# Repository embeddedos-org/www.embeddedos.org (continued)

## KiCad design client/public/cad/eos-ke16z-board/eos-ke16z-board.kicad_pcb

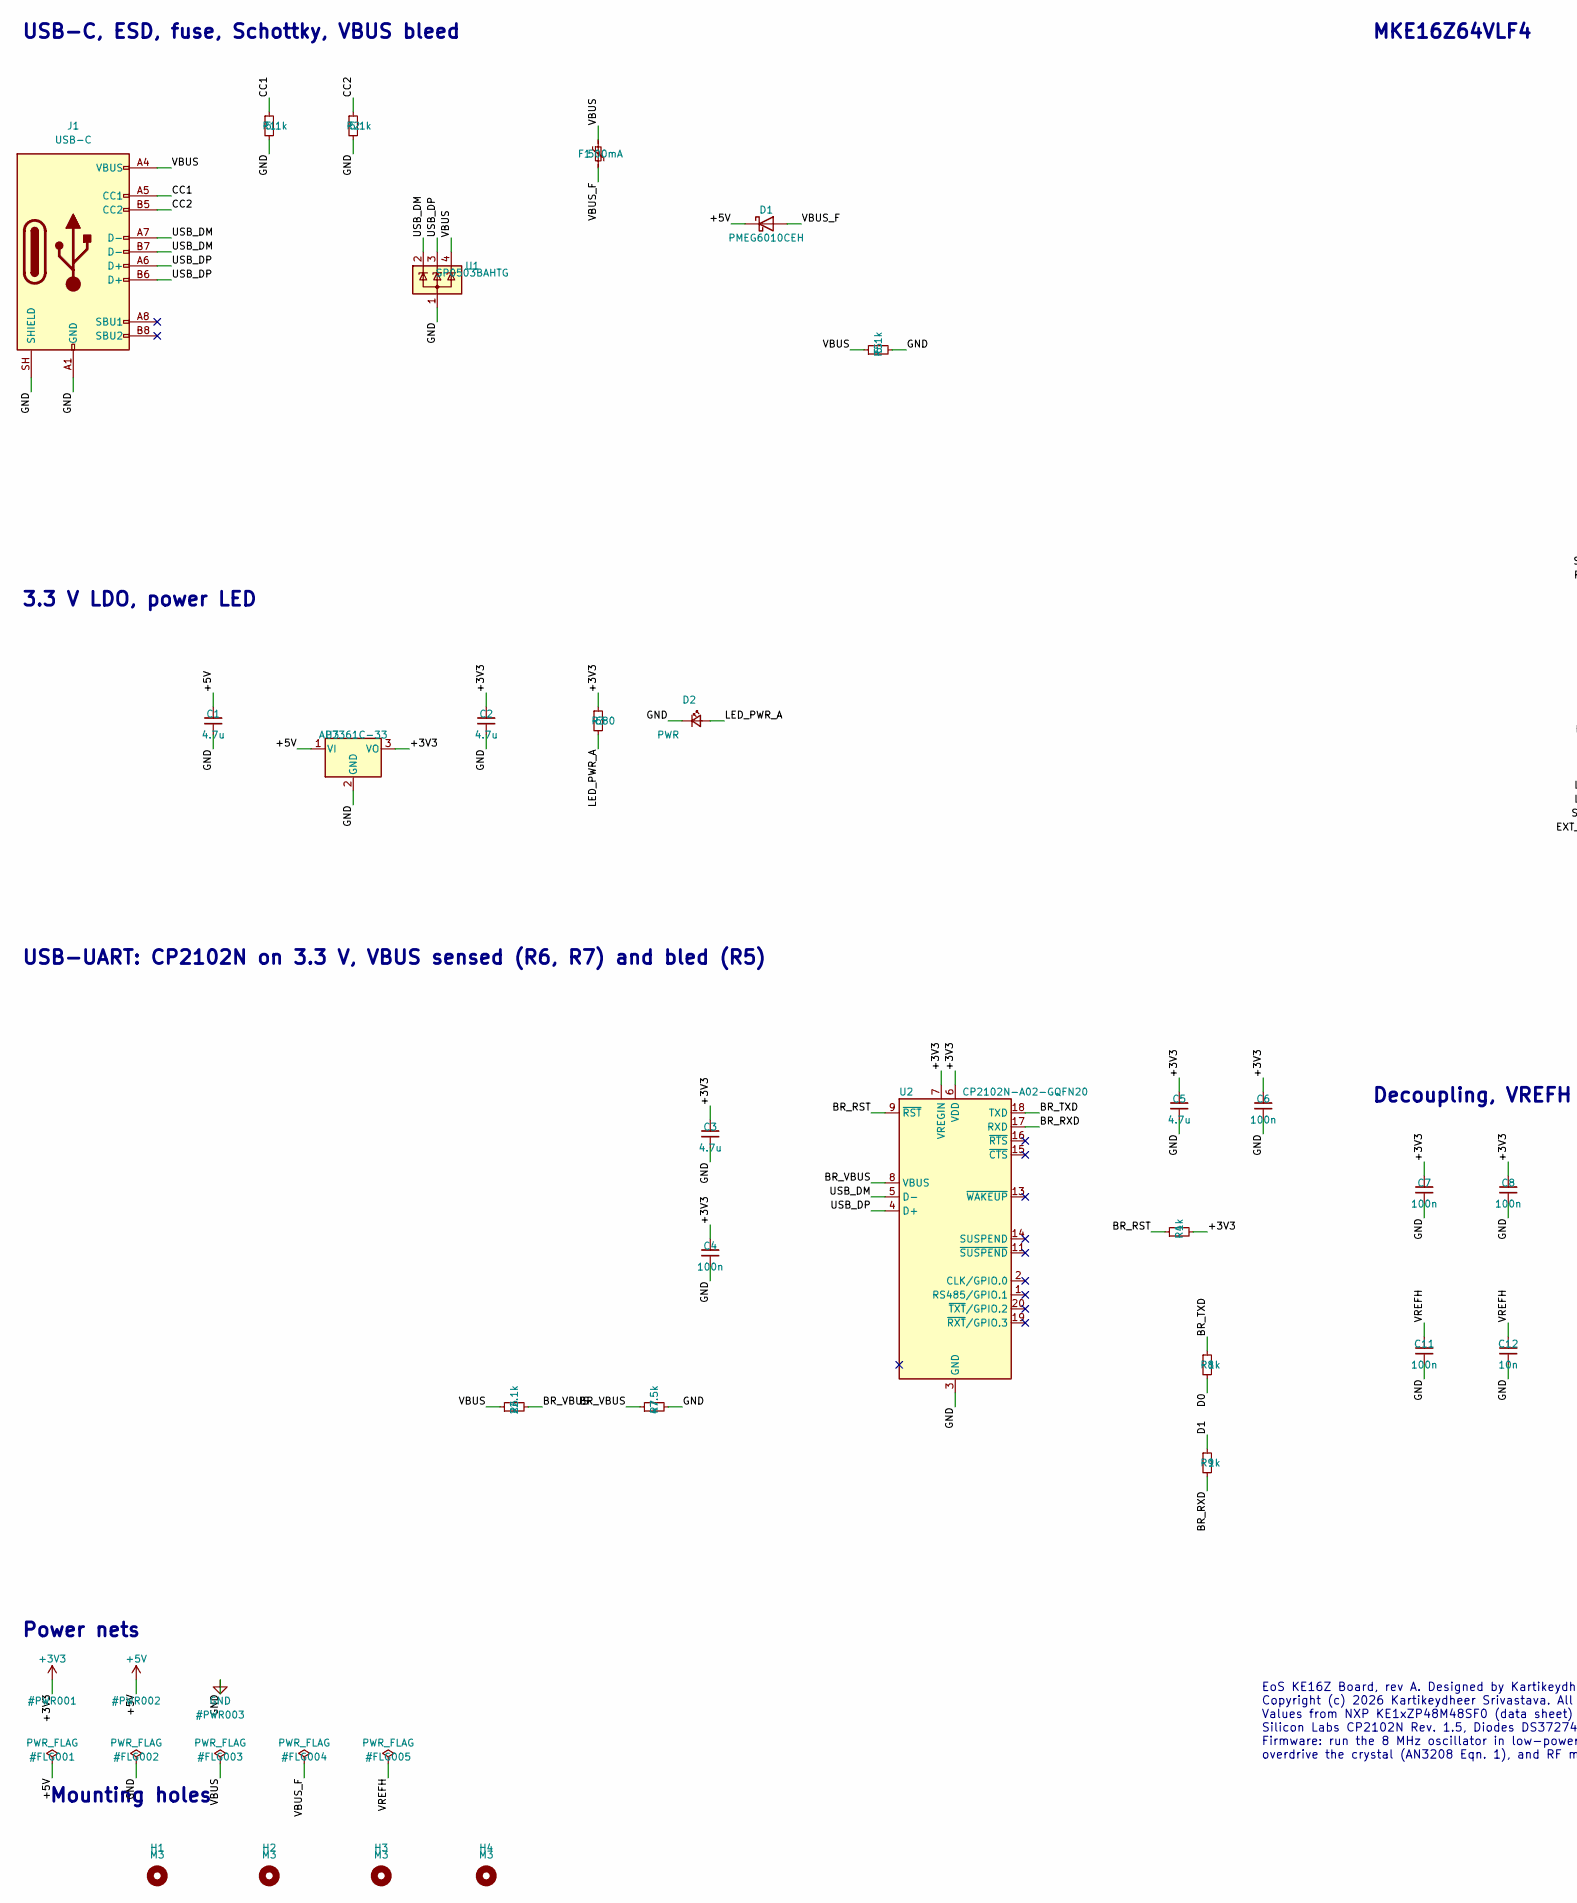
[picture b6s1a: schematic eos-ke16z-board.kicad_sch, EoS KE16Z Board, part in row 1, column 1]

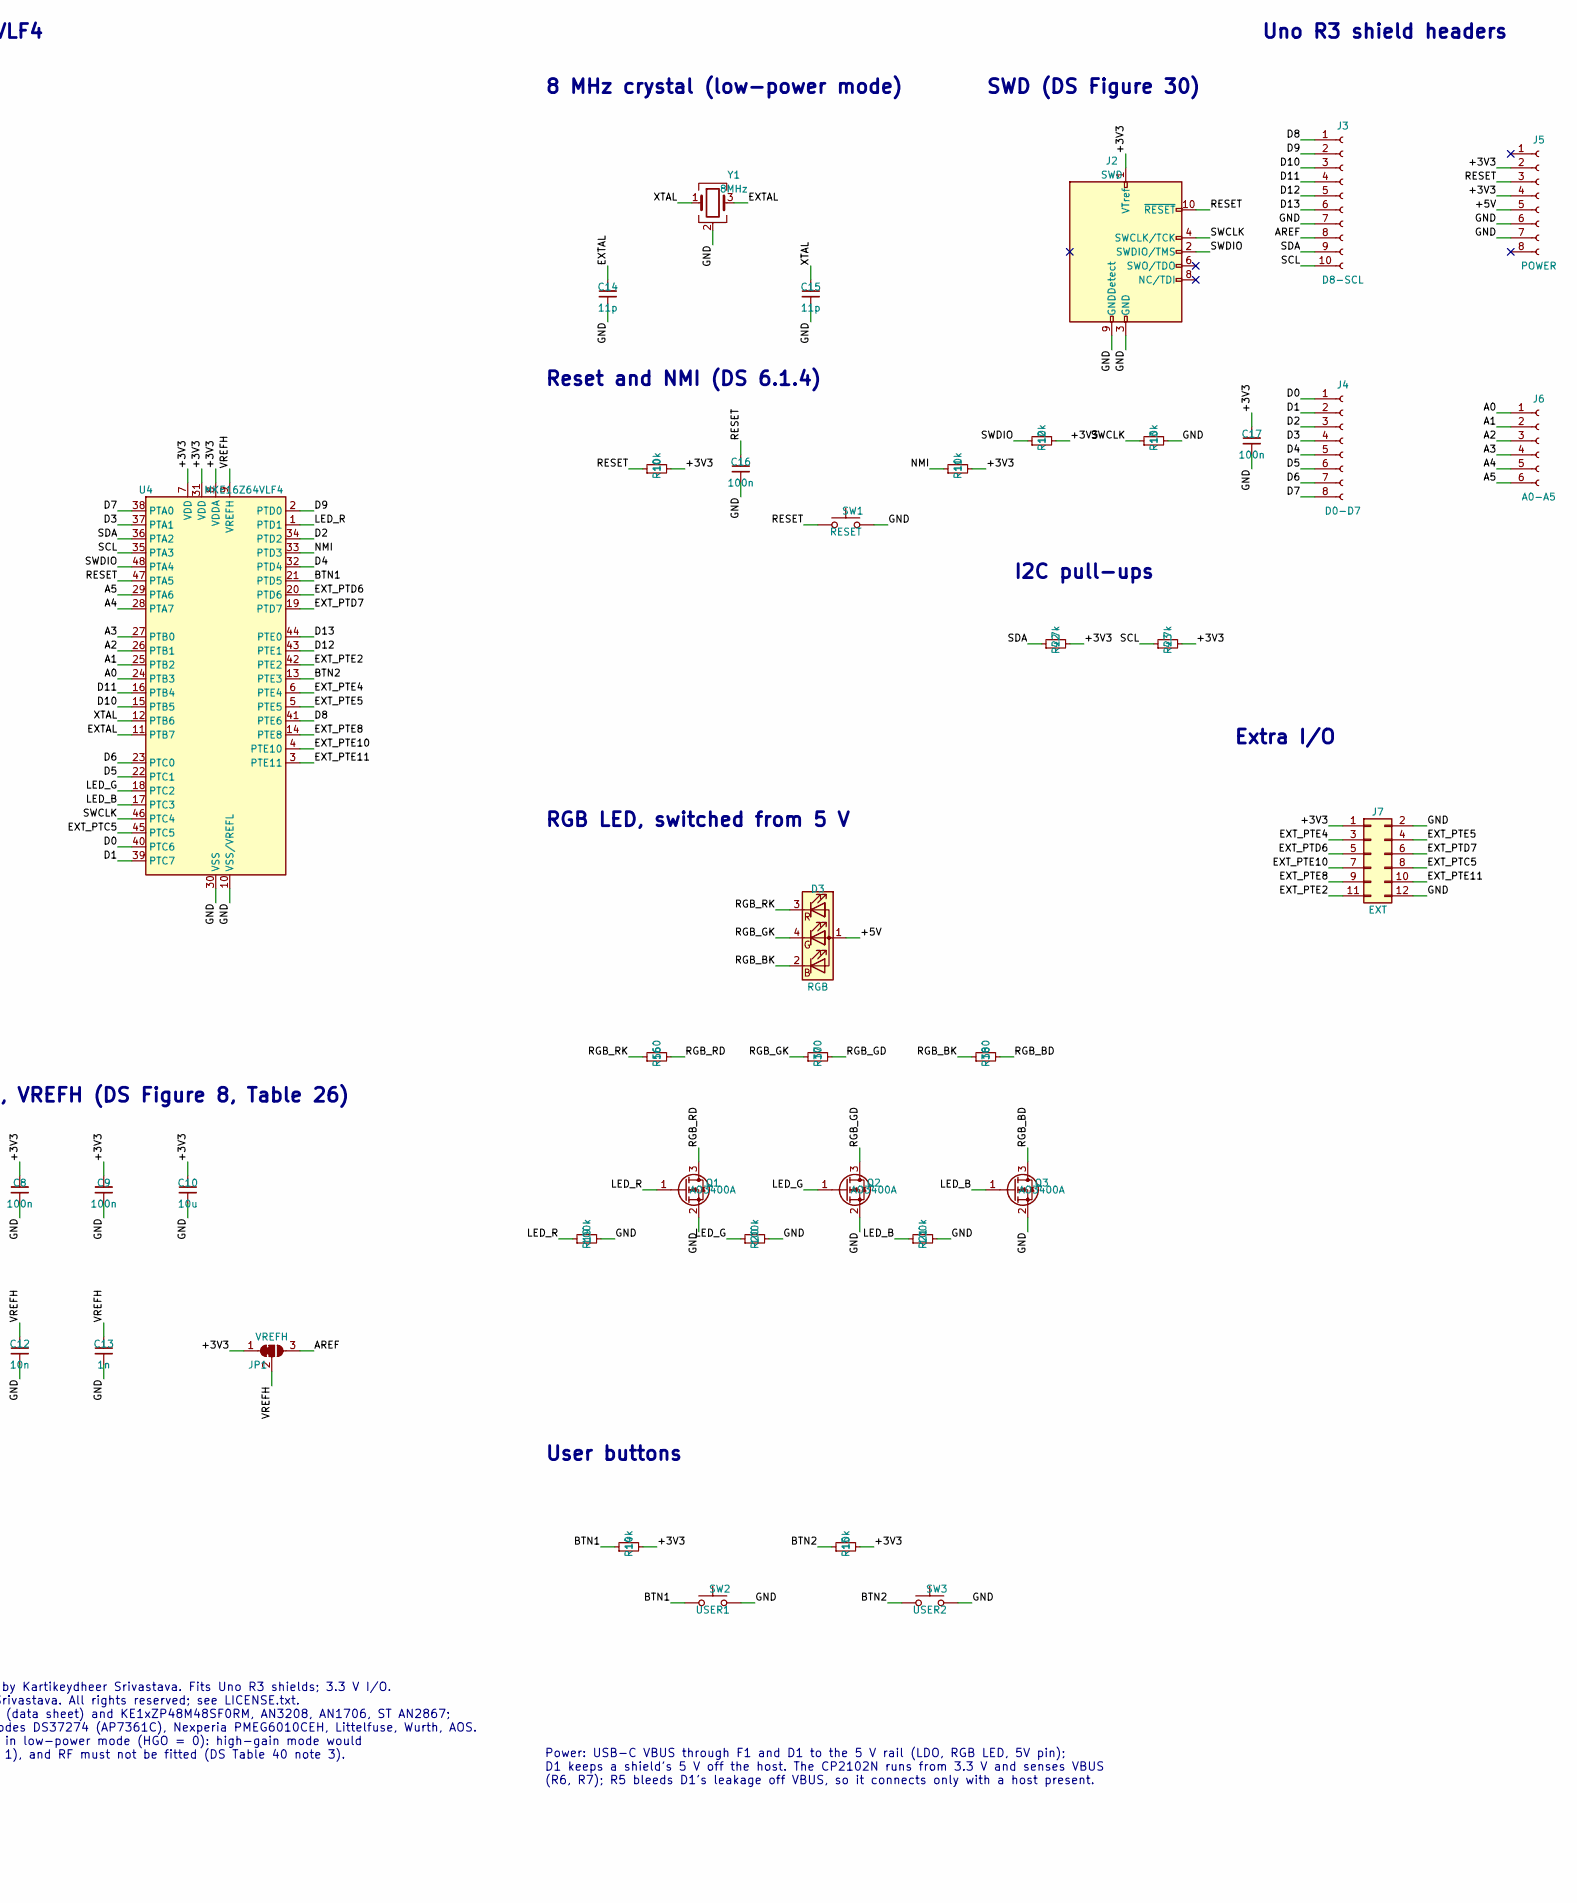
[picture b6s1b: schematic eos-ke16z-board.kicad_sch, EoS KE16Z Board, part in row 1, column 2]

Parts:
C1: 4.7u; C_0805_2012Metric; MPN GRM219R61E475KA73D
C2, C3, C5: 4.7u; C_0805_2012Metric; MPN GRM21BR71A475KE51L
C4, C6, C7, C8, C9, C11, C16, C17: 100n; C_0402_1005Metric; MPN GRM155R71C104KA88D
C10: 10u; C_0805_2012Metric; MPN GRM21BR61C106KE15L
C12: 10n; C_0402_1005Metric; MPN GRM155R71H103KA88D
C13: 1n; C_0402_1005Metric; MPN GRM1555C1H102JA01D
C14, C15: 11p; C_0402_1005Metric; MPN GJM1555C1H110JB01D
D1: PMEG6010CEH; D_SOD-123F; MPN PMEG6010CEH
D2: PWR; LED_0603_1608Metric; MPN APTD1608LCGCK
D3: RGB; LED_RGB_Wuerth-PLCC4_3.2x2.8mm_150141M173100; MPN 150141M173100
F1: 500mA; Fuse_1206_3216Metric; MPN 1206L050YR
H1, H2, H3, H4: M3; MountingHole_3.2mm_M3_ISO14580
J1: USB-C; USB_C_Receptacle_HRO_TYPE-C-31-M-12; MPN TYPE-C-31-M-12
J2: SWD; PinHeader_2x05_P1.27mm_Vertical_SMD; MPN FTSH-105-01-L-DV-K
J3: D8-SCL; PinSocket_1x10_P2.54mm_Vertical; MPN SSW-110-01-T-S
J4: D0-D7; PinSocket_1x08_P2.54mm_Vertical; MPN SSW-108-01-T-S
J5: POWER; PinSocket_1x08_P2.54mm_Vertical; MPN SSW-108-01-T-S
J6: A0-A5; PinSocket_1x06_P2.54mm_Vertical; MPN SSW-106-01-T-S
J7: EXT; PinHeader_2x06_P2.54mm_Vertical; MPN TSW-106-07-G-D
JP1: VREFH; SolderJumper-3_P1.3mm_Bridged12_RoundedPad1.0x1.5mm
Q1, Q2, Q3: AO3400A; SOT-23; MPN AO3400A
R1, R2, R5: 5.1k; R_0402_1005Metric; MPN RC0402FR-075K1L
R3: 680; R_0402_1005Metric; MPN RC0402FR-07680RL
R4, R8, R9: 1k; R_0402_1005Metric; MPN RC0402FR-071KL
R6: 22.1k; R_0402_1005Metric; MPN RC0402FR-0722K1L
R7: 47.5k; R_0402_1005Metric; MPN RC0402FR-0747K5L
R10, R11, R12, R13, R14, R15: 10k; R_0402_1005Metric; MPN RC0402FR-0710KL
R16: 560; R_0402_1005Metric; MPN RC0402FR-07560RL
R17, R18: 300; R_0402_1005Metric; MPN RC0402FR-07300RL
R19, R20, R21: 100k; R_0402_1005Metric; MPN RC0402FR-07100KL
R22, R23: 4.7k; R_0402_1005Metric; MPN RC0402FR-074K7L
SW1: RESET; SW_Push_1P1T_NO_CK_KMR2; MPN KMR221G LFS
SW2: USER1; SW_Push_1P1T_NO_CK_KMR2; MPN KMR221G LFS
SW3: USER2; SW_Push_1P1T_NO_CK_KMR2; MPN KMR221G LFS
U1: SP0503BAHTG; SOT-143; MPN SP0503BAHTG
U2: CP2102N-A02-GQFN20; SiliconLabs_QFN-20-1EP_3x3mm_P0.5mm_EP1.8x1.8mm; MPN CP2102N-A02-GQFN20
U3: AP7361C-33; SOT-223-3_TabPin2; MPN AP7361C-33E-13
U4: MKE16Z64VLF4; LQFP-48_7x7mm_P0.5mm; MPN MKE16Z64VLF4
Y1: 8MHz; Crystal_SMD_5032-4Pin_5.0x3.2mm; MPN ECS-80-10-30B-CWN-TR

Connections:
+3V3: C2.1, C3.1, C4.1, C5.1, C6.1, C7.1, C8.1, C9.1, C10.1, C17.1, J2.1 (VTref), J5.2, J5.4, J7.1, JP1.1 (A), R3.1, R4.2, R10.2, R11.2, R12.2, R14.2, R15.2, R22.2, R23.2, U2.6 (VDD), U2.7 (VREGIN), U3.3 (VO), U4.7 (VDD), U4.8 (VDDA), U4.31 (VDD)
+5V: C1.1, D1.1 (K), D3.1 (A), J5.5, U3.1 (VI)
/A0: J6.1, U4.24 (PTB3)
/A1: J6.2, U4.25 (PTB2)
/A2: J6.3, U4.26 (PTB1)
/A3: J6.4, U4.27 (PTB0)
/A4: J6.5, U4.28 (PTA7)
/A5: J6.6, U4.29 (PTA6)
/AREF: J3.8, JP1.3 (B)
/BR_RST: R4.1, U2.9 (~RST)
/BR_RXD: R9.2, U2.17 (RXD)
/BR_TXD: R8.1, U2.18 (TXD)
/BR_VBUS: R6.2, R7.1, U2.8 (VBUS)
/BTN1: R14.1, SW2.1, U4.21 (PTD5)
/BTN2: R15.1, SW3.1, U4.13 (PTE3)
/CC1: J1.A5 (CC1), R1.1
/CC2: J1.B5 (CC2), R2.1
/D0: J4.1, R8.2, U4.40 (PTC6)
/D1: J4.2, R9.1, U4.39 (PTC7)
/D2: J4.3, U4.34 (PTD2)
/D3: J4.4, U4.37 (PTA1)
/D4: J4.5, U4.32 (PTD4)
/D5: J4.6, U4.22 (PTC1)
/D6: J4.7, U4.23 (PTC0)
/D7: J4.8, U4.38 (PTA0)
/D8: J3.1, U4.41 (PTE6)
/D9: J3.2, U4.2 (PTD0)
/D10: J3.3, U4.15 (PTB5)
/D11: J3.4, U4.16 (PTB4)
/D12: J3.5, U4.43 (PTE1)
/D13: J3.6, U4.44 (PTE0)
/EXTAL: C14.1, U4.11 (PTB7), Y1.3
/EXT_PTC5: J7.8, U4.45 (PTC5)
/EXT_PTD6: J7.5, U4.20 (PTD6)
/EXT_PTD7: J7.6, U4.19 (PTD7)
/EXT_PTE2: J7.11, U4.42 (PTE2)
/EXT_PTE4: J7.3, U4.6 (PTE4)
/EXT_PTE5: J7.4, U4.5 (PTE5)
/EXT_PTE8: J7.9, U4.14 (PTE8)
/EXT_PTE10: J7.7, U4.4 (PTE10)
/EXT_PTE11: J7.10, U4.3 (PTE11)
/LED_B: Q3.1 (G), R21.1, U4.17 (PTC3)
/LED_G: Q2.1 (G), R20.1, U4.18 (PTC2)
/LED_PWR_A: D2.2 (A), R3.2
/LED_R: Q1.1 (G), R19.1, U4.1 (PTD1)
/NMI: R11.1, U4.33 (PTD3)
/RESET: C16.1, J2.10 (~RESET), J5.3, R10.1, SW1.1, U4.47 (PTA5)
/RGB_BD: Q3.3 (D), R18.2
/RGB_BK: D3.2 (BK), R18.1
/RGB_GD: Q2.3 (D), R17.2
/RGB_GK: D3.4 (GK), R17.1
/RGB_RD: Q1.3 (D), R16.2
/RGB_RK: D3.3 (RK), R16.1
/SCL: J3.10, R23.1, U4.35 (PTA3)
/SDA: J3.9, R22.1, U4.36 (PTA2)
/SWCLK: J2.4 (SWCLK/TCK), R13.1, U4.46 (PTC4)
/SWDIO: J2.2 (SWDIO/TMS), R12.1, U4.48 (PTA4)
/USB_DM: J1.A7 (D-), J1.B7 (D-), U1.2 (K), U2.5 (D-)
/USB_DP: J1.A6 (D+), J1.B6 (D+), U1.3 (K), U2.4 (D+)
/VBUS: F1.1, J1.A4 (VBUS), J1.A9 (VBUS), J1.B4 (VBUS), J1.B9 (VBUS), R5.1, R6.1, U1.4 (K)
/VBUS_F: D1.2 (A), F1.2
/VREFH: C11.1, C12.1, C13.1, JP1.2 (C), U4.9 (VREFH)
/XTAL: C15.1, U4.12 (PTB6), Y1.1
GND: C1.2, C2.2, C3.2, C4.2, C5.2, C6.2, C7.2, C8.2, C9.2, C10.2, C11.2, C12.2, C13.2, C14.2, C15.2, C16.2, C17.2, D2.1 (K), J1.A1 (GND), J1.A12 (GND), J1.B1 (GND), J1.B12 (GND), J1.SH (SHIELD), J2.3 (GND), J2.5 (GND), J2.9 (GNDDetect), J3.7, J5.6, J5.7, J7.2, J7.12, Q1.2 (S), Q2.2 (S), Q3.2 (S), R1.2, R2.2, R5.2, R7.2, R13.2, R19.2, R20.2, R21.2, SW1.2, SW2.2, SW3.2, U1.1 (A), U2.3 (GND), U2.12 (GND), U2.21 (GND), U3.2 (GND), U4.10 (VSS/VREFL), U4.30 (VSS), Y1.2 (G), Y1.4 (G)

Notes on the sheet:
USB-C, ESD, fuse, Schottky, VBUS bleed
3.3 V LDO, power LED
USB-UART: CP2102N on 3.3 V, VBUS sensed (R6, R7) and bled (R5)
MKE16Z64VLF4
Decoupling, VREFH (DS Figure 8, Table 26)
8 MHz crystal (low-power mode)
Reset and NMI (DS 6.1.4)
SWD (DS Figure 30)
RGB LED, switched from 5 V
User buttons
Uno R3 shield headers
I2C pull-ups
Extra I/O
Mounting holes
Power nets
EoS KE16Z Board, rev A. Designed by Kartikeydheer Srivastava. Fits Uno R3 shields; 3.3 V I/O. Copyright (c) 2026 Kartikeydheer Srivastava. All rights reserved; see LICENSE.txt. Values from NXP KE1xZP48M48SF0 (data sheet) and KE1xZP48M48SF0RM, AN3208, AN1706, ST AN2867; Silicon Labs CP2102N Rev. 1.5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
Power: USB-C VBUS through F1 and D1 to the 5 V rail (LDO, RGB LED, 5V pin); D1 keeps a shield's 5 V off the host. The CP2102N runs from 3.3 V and senses VBUS (R6, R7); R5 bleeds D1's leakage off VBUS, so it connects only with a host present.

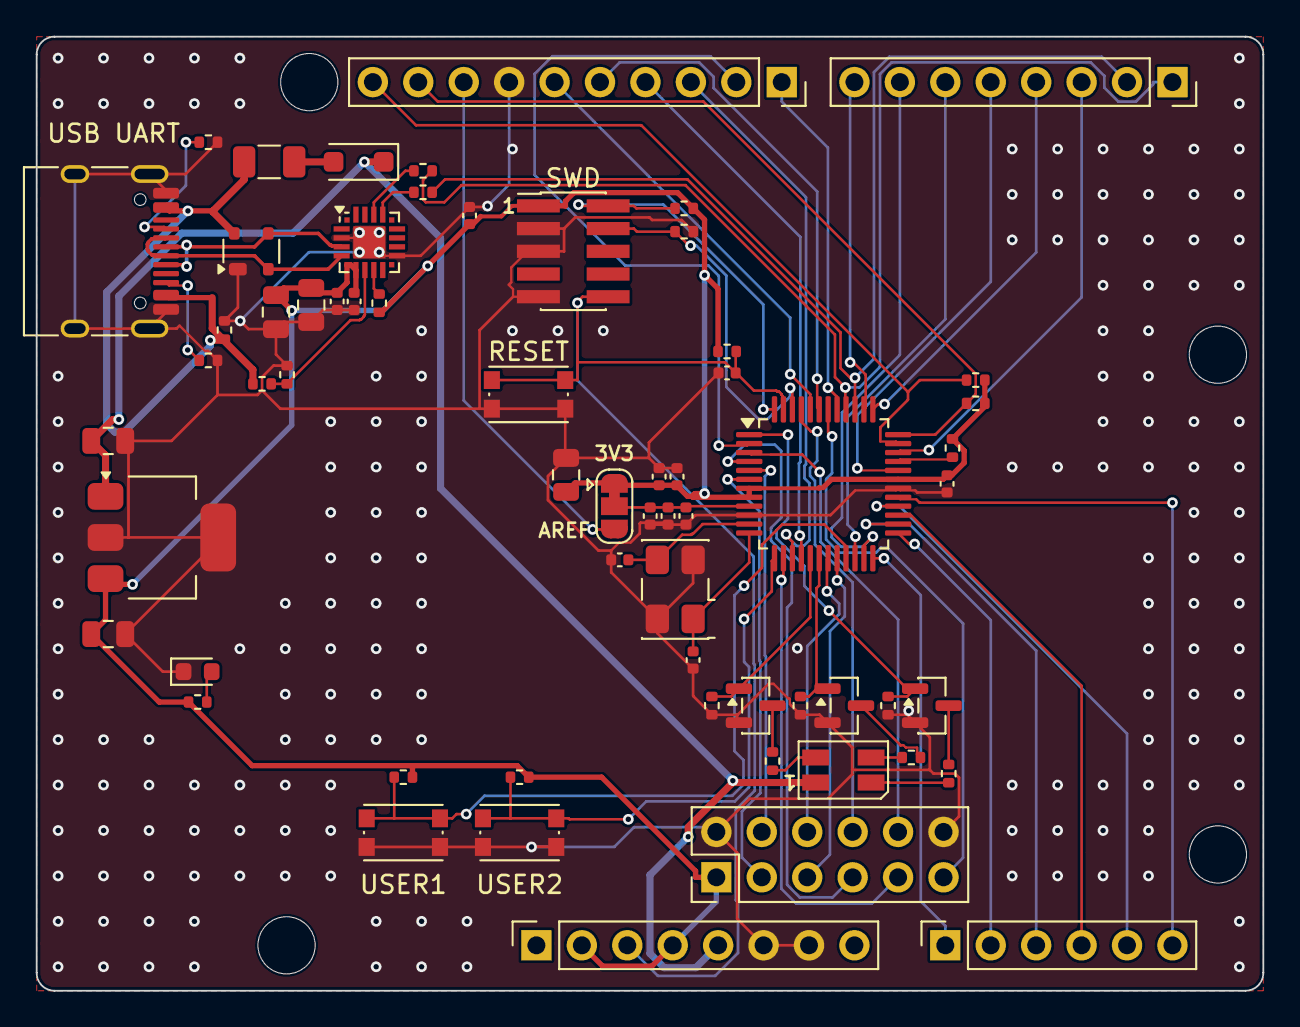
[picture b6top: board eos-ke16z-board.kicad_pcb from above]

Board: 2 copper layers, 68.6 x 53.3 mm, 67 parts (1 on the bottom side), 64 nets.
